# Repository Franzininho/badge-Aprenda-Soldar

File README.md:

# Badge - Aprenda Soldar

O badge Aprenda Soldar foi desenvolvido para oficinas de solda onde os participantes dão os primeiros passos com o uso de ferramentas e no conhecimento dos componentes eletrônicos e circuito da placa. Com poucos componentes, esse badge permite que qualquer pessoa aprenda a soldar e se divertir.

O circuito escolhido para esse badge, foi o clássico multivibrador astável com trasistores.

A placa foi desenhada no [Kicad](https://kicad-pcb.org/) e os arquivos estão disponíveis no github. A placa possui duas camadas e necessita de metalização de furos para acabamento.

A seguir é apresentada a lista de materiais:

- 2 x Resistor 470k
- 2 x Resistor 470 Ohm
- 2 x transistor BC548
- 1x LED 3mm verde
- 1x LED 3mm amarelo
- 2 x Capacitor 10uF x 16V
- 1 x Suporte para bateria CR2032
- 1 x Bateria CR2032

Esse projeto foi um dos vencedores do [Contest badge Love](https://www.hackster.io/contests/BadgeLove) na categoria The Badge of Hope, promovido pelo [Hackster](https://www.hackster.io/fabiosouza/badge-aprenda-soldar-learn-to-solder-1f082d)

O projeto é open hardware e foi publicado sob a licença [Creative Commons Attribution Share Alike 4.0 International](https://github.com/Open-Badges/badge00/blob/master/LICENSE)

Esse projeto faz parte da família de placas Franzininho e foi desenvolvido por Fábio Souza, idealizador do projeto. Para mais detalhes acesse o site da [Franzininho](https://franzininho.com.br/)

Para adquirir placas e kits do badge Aprenda Soldar, entre em contato conosco: [contato@franzininho.com.br](contato@franzininho.com.br)

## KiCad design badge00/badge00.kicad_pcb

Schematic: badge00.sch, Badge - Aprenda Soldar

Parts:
BT1: Battery_Cell; CR2032_HOLDER
C1, C2: 10uF; CP_Radial_D5.0mm_P2.50mm
D1, D2: LED; LED_D3.0mm
Q1, Q2: BC548; TO-92_Inline_Wide
R1, R4: 470R; R_Axial_DIN0207_L6.3mm_D2.5mm_P10.16mm_Horizontal
R2, R3: 47k; R_Axial_DIN0207_L6.3mm_D2.5mm_P10.16mm_Horizontal
SW1: SW_SPDT; SW_HH_SS12D07-G4-2

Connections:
unnamed: BT1.1, R1.1, R2.1, R3.1, R4.1
unnamed: BT1.2, SW1.1
unnamed: C1.1, D1.1, Q1.1 (C)
unnamed: C1.2, Q2.2 (B), R2.2
unnamed: C2.1, D2.1, Q2.1 (C)
unnamed: C2.2, Q1.2 (B), R3.2
unnamed: D1.2, R1.2
unnamed: D2.2, R4.2
unnamed: Q1.3 (E), Q2.3 (E), SW1.2

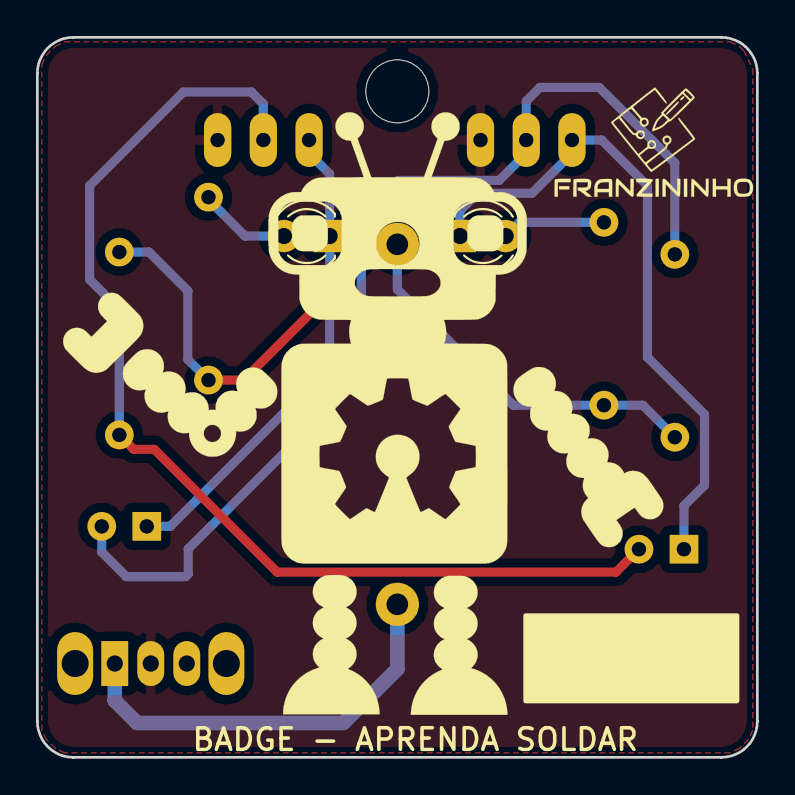
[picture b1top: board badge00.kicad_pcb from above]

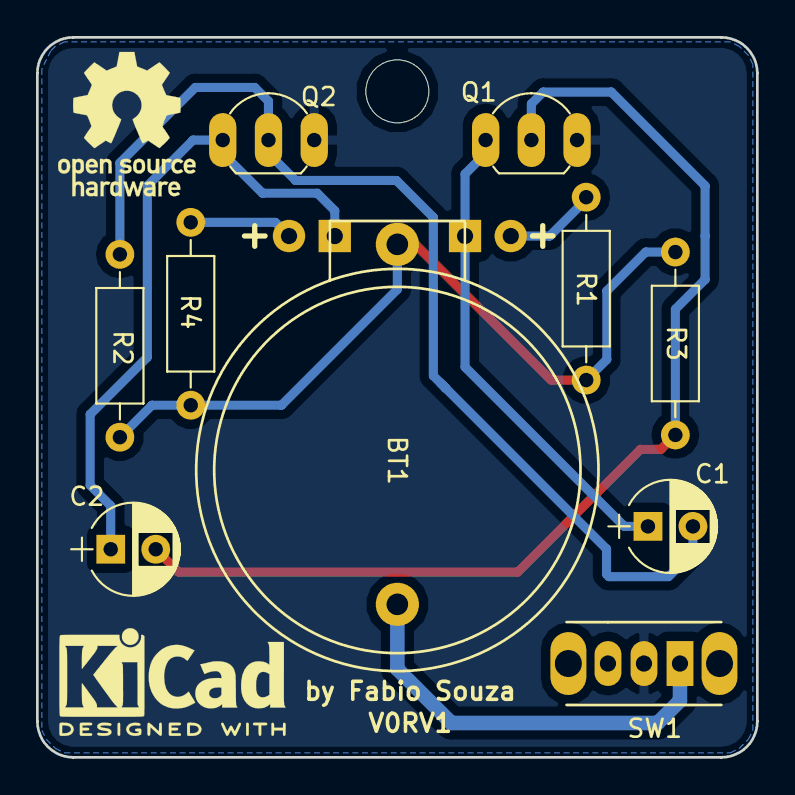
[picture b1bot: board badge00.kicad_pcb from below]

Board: 2 copper layers, 40.0 x 40.0 mm, 12 parts (10 on the bottom side), 9 nets.

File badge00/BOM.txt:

Ref		Descrição									Quatidade
placa	Placa Badge00									1
Q1,Q2	Transistor BC548								2
C1, C2	Capacitor Eletrolítico 10uF x 25 V				2
R1,r4	Resistor 470R									2
R2,R3	Resistor 47K									2
BT1		Suporte de bateria CR2032						1
BT1		Bateria CR2032									1
LED1	Led Amarelo 3mm									1
LED2	LED Verde 3mm									1
S1		Chave HH - SS12D07								1

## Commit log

2018-07-06 kicad files
2018-07-06 licença
2018-07-31 upadate schematic
2018-08-01 documentação
2018-09-20 re-layout
2018-09-25 switch
2019-02-19 doc update
2019-03-01 BOM txt
2019-03-01 Move BOM
2019-12-04 atualiazação do readme
2019-12-04 formatação do readme
2019-12-04 Ajuste de arquivos na pasta e Readme
2019-12-04 correção de erro ortográfico
2019-12-04 Adicionada pasta com fotos e imagens para documentação
2019-12-04 Ajuste de links e e-mail
